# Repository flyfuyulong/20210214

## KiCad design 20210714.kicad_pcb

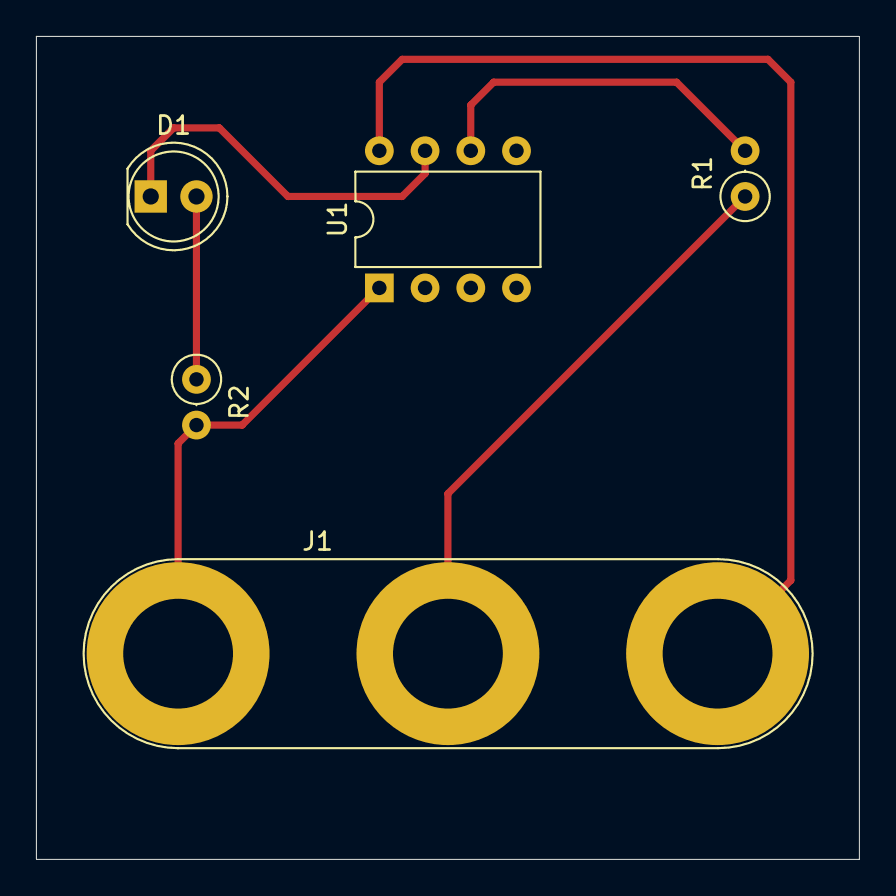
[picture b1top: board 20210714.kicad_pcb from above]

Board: 2 copper layers, 45.7 x 45.7 mm, 5 parts (0 on the bottom side), 6 nets.

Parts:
D1: LED; LED_D5.0mm
J1: MYCONN3; Banana_Jack_3Pin
R1: 100; R_Axial_DIN0207_L6.3mm_D2.5mm_P2.54mm_Vertical
R2: 1K; R_Axial_DIN0207_L6.3mm_D2.5mm_P2.54mm_Vertical
U1: PIC12C508A-ISN; DIP-8_W7.62mm

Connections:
/INPUT: R1.2, U1.6
GND: J1.3, U1.8
unnamed: D1.1, U1.7
unnamed: D1.2, R2.1
unnamed: J1.2, R1.1
VCC: J1.1, R2.2, U1.1

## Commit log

2021-07-15 V1.0.0
